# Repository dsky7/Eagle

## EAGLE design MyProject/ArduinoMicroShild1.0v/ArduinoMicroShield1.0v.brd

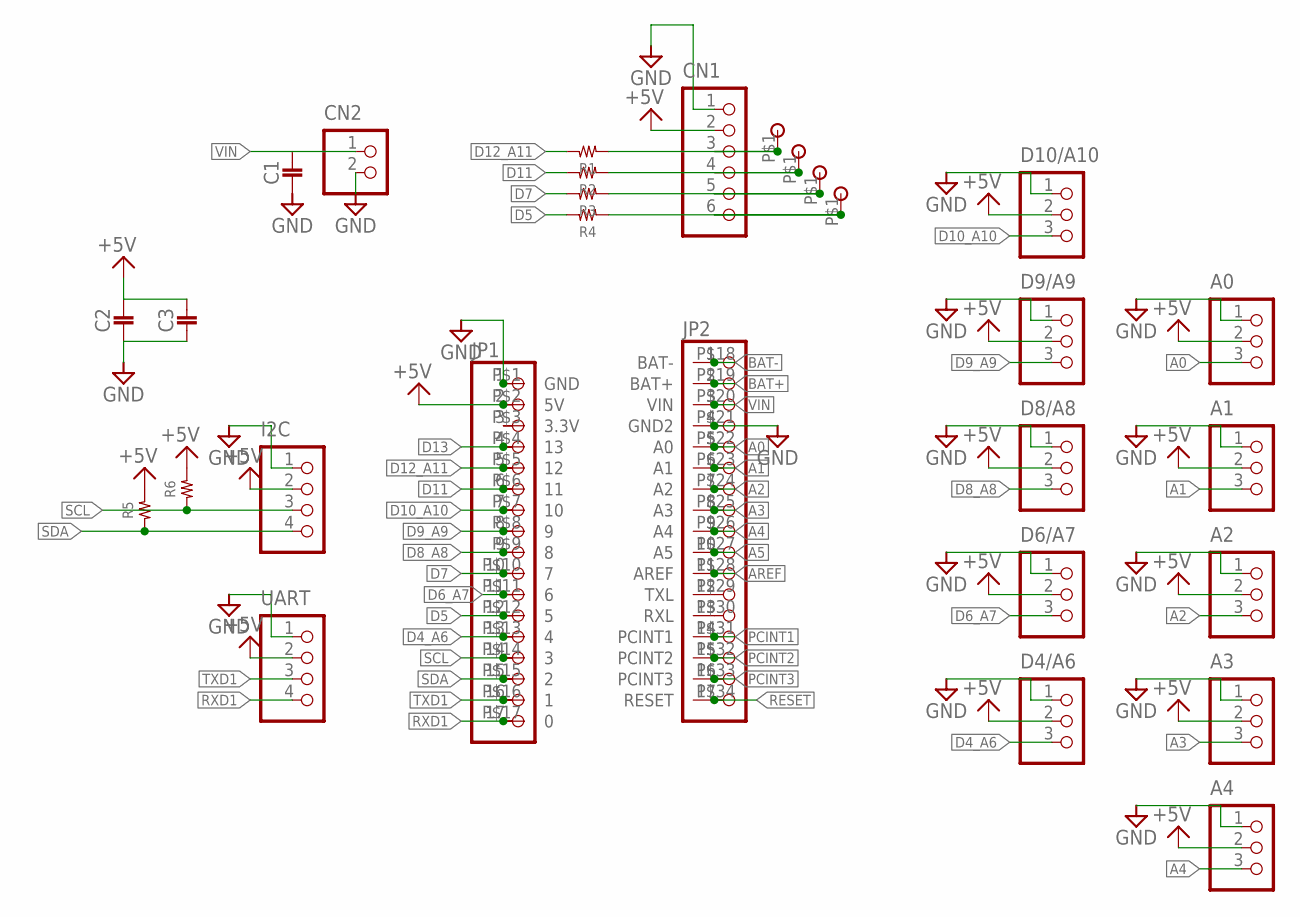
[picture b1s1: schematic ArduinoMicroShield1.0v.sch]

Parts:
A0, A1, A2, A3, A4: B3B-PH-K-S
C1, C2, C3: 1608
CN1: B6B-PH-K-S
CN2: S2B-PH-K-S
D4/A6, D6/A7, D8/A8, D9/A9, D10/A10: B3B-PH-K-S
I2C: B4B-PH-K-S
JP1, JP2: PINHD-1X17; 1X17
R1, R2, R3, R4, R5, R6: RESISTOR__SMD; 1608
U$1: ARDUINO_ASTAR_MICRO
U$31, U$32, U$36, U$37: CHECK_0.8MM
UART: B4B-PH-K-S

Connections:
+5V: A0.2, A1.2, A2.2, A3.2, A4.2, C2.P$1 (1), C3.P$1 (1), CN1.2, D4/A6.2, D6/A7.2, D8/A8.2, D9/A9.2, D10/A10.2, I2C.2, JP1.2, R5.2, R6.2, U$1.P$2 (5V), UART.2
A0: A0.3, JP2.5, U$1.P$22 (A0)
A1: A1.3, JP2.6, U$1.P$23 (A1)
A2: A2.3, JP2.7, U$1.P$24 (A2)
A3: A3.3, JP2.8, U$1.P$25 (A3)
A4: A4.3, JP2.9, U$1.P$26 (A4)
A5: JP2.10, U$1.P$27 (A5)
AREF: JP2.11, U$1.P$28 (AREF)
BAT+: JP2.2, U$1.P$19 (BAT+)
BAT-: JP2.1, U$1.P$18 (BAT-)
D4_A6: D4/A6.3, JP1.13, U$1.P$13 (4)
D5: JP1.12, R4.2, U$1.P$12 (5)
D6_A7: D6/A7.3, JP1.11, U$1.P$11 (6)
D7: JP1.10, R3.2, U$1.P$10 (7)
D8_A8: D8/A8.3, JP1.9, U$1.P$9 (8)
D9_A9: D9/A9.3, JP1.8, U$1.P$8 (9)
D10_A10: D10/A10.3, JP1.7, U$1.P$7 (10)
D11: JP1.6, R2.2, U$1.P$6 (11)
D12_A11: JP1.5, R1.2, U$1.P$5 (12)
D13: JP1.4, U$1.P$4 (13)
GND: A0.1, A1.1, A2.1, A3.1, A4.1, C1.P$2 (2), C2.P$2 (2), C3.P$2 (2), CN1.1, CN2.2, D4/A6.1, D6/A7.1, D8/A8.1, D9/A9.1, D10/A10.1, I2C.1, JP1.1, JP2.4, U$1.P$1 (GND), U$1.P$21 (GND2), UART.1
unnamed: CN1.6, R4.1, U$37.P$1
unnamed: CN1.5, R3.1, U$36.P$1
unnamed: CN1.4, R2.1, U$32.P$1
unnamed: CN1.3, R1.1, U$31.P$1
unnamed: JP1.3, U$1.P$3 (3.3V)
unnamed: JP2.12, U$1.P$29 (TXL)
unnamed: JP2.13, U$1.P$30 (RXL)
PCINT1: JP2.14, U$1.P$31 (PCINT1)
PCINT2: JP2.15, U$1.P$32 (PCINT2)
PCINT3: JP2.16, U$1.P$33 (PCINT3)
RESET: JP2.17, U$1.P$34 (RESET)
RXD1: JP1.17, U$1.P$17 (0), UART.4
SCL: I2C.3, JP1.14, R6.1, U$1.P$14 (3)
SDA: I2C.4, JP1.15, R5.1, U$1.P$15 (2)
TXD1: JP1.16, U$1.P$16 (1), UART.3
VIN: C1.P$1 (1), CN2.1, JP2.3, U$1.P$20 (VIN)

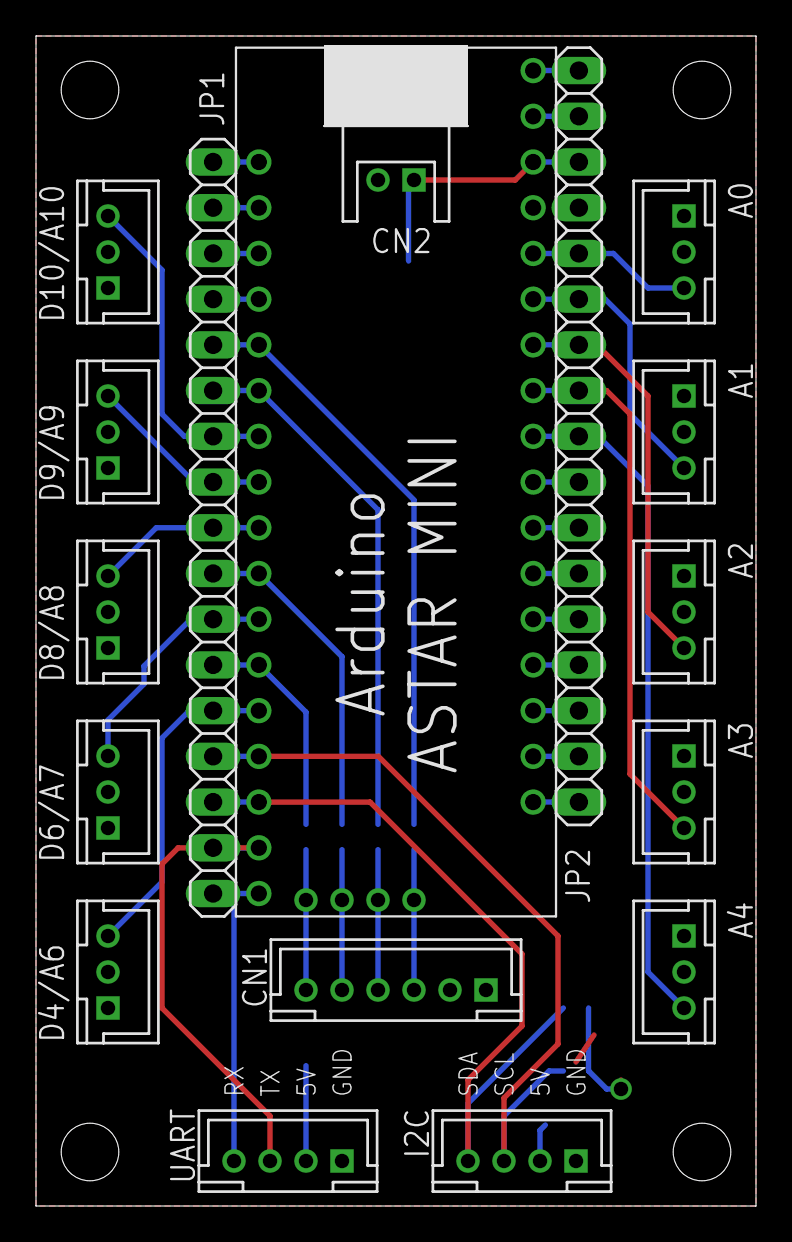
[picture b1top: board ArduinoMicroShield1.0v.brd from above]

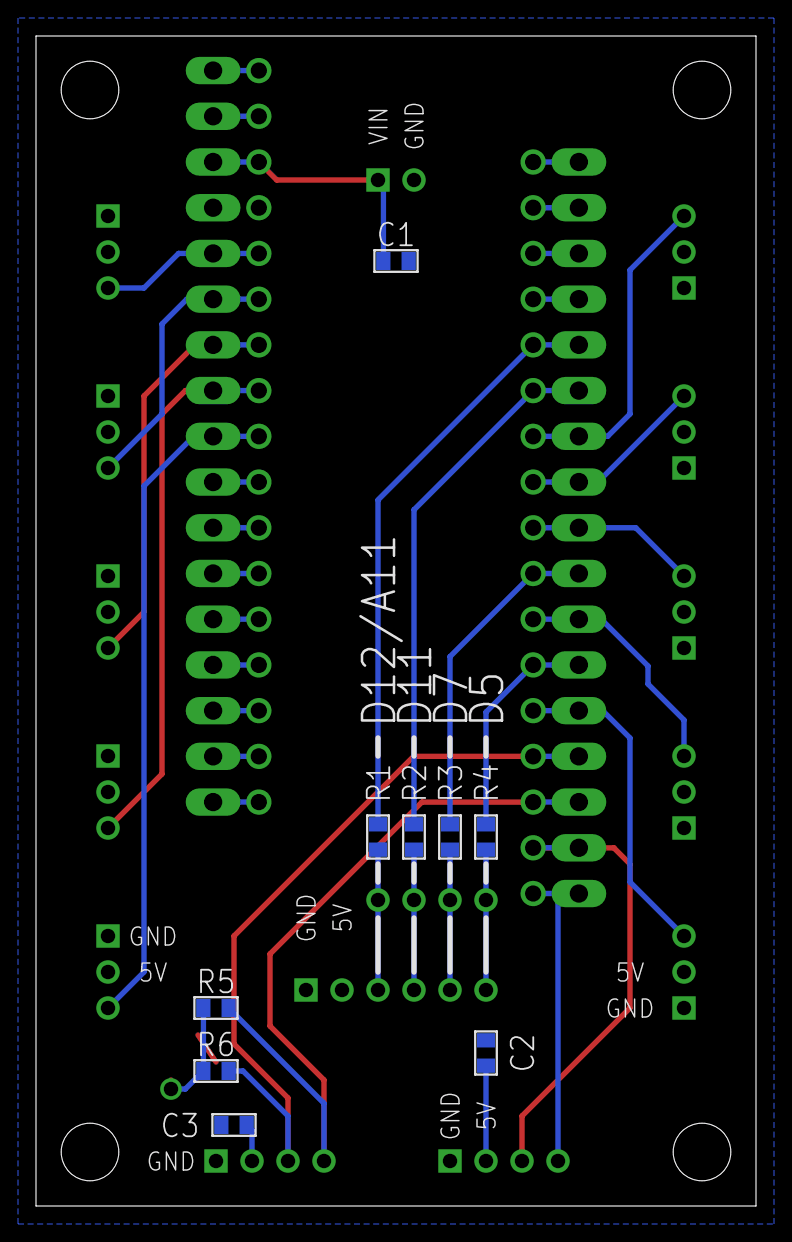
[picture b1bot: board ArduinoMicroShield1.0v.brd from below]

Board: 2 copper layers, 40.0 x 65.0 mm, 31 parts (9 on the bottom side), 37 nets.

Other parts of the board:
DRILEGEND: DRILEGEND

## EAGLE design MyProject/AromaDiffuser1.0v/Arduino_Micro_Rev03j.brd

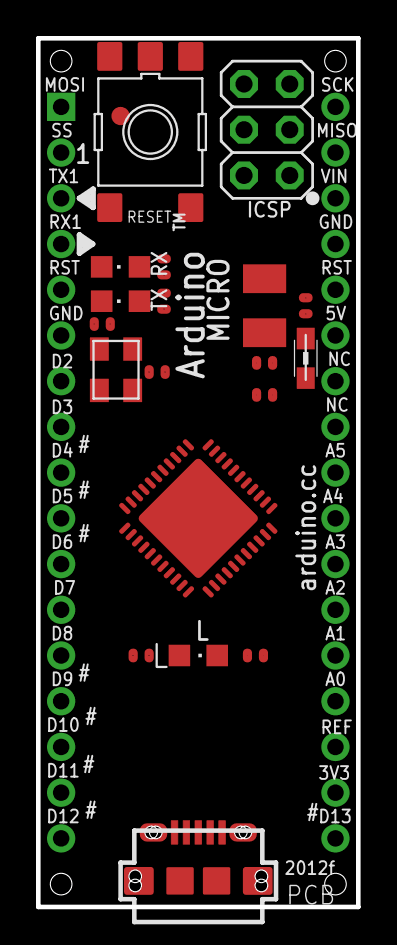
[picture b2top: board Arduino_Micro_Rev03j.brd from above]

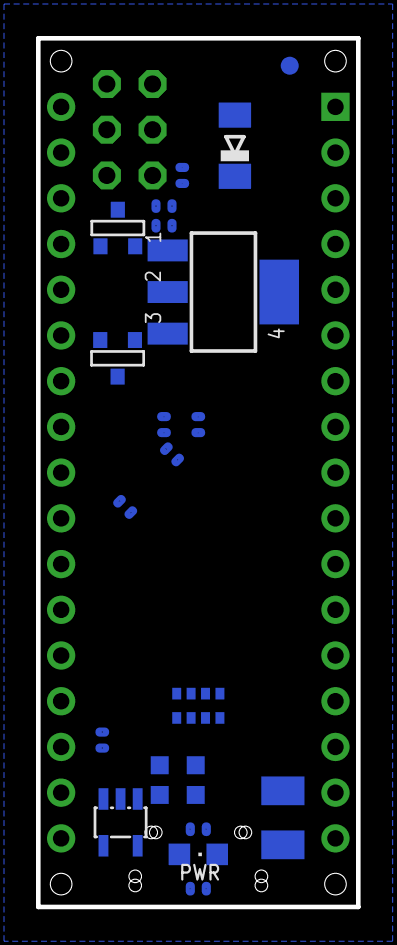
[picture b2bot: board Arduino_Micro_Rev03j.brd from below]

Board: 4 copper layers, 17.8 x 48.3 mm, 44 parts (21 on the bottom side), 47 nets, no tracks yet.

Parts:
C1, C2, C6, C9, C10, C11: 100n; C0402
C3, C14: 22u; SMC_B
C4, C5, C7: 1uF; C0402
C12, C13: 22pF; C0402
D2: CD1206-S01575; MINIMELF
J3: USB-MICRO!!!; CON2_USB_MICRO_B_AT
J4: 3x2M; 2X03
J5: HEAD17-NOSS
J6: HEAD17-NOSS-1
L: green; CHIPLED_0805
L2: MH2029-300Y; 0805
ON: blue; CHIPLED_0805
R1, R2, R4, R9: 10K; R0402
R5, R6, R7, R8: 1K; R0402
RESET: TS42
RP3: 22R; CAY16
RX: yellow; CHIPLED_0805
T1: FDN340P/PMV48XP; SOT-23
T2: PMV48XP; SOT-23
TX: yellow; CHIPLED_0805
U1: ATMEGA32U4-XUMU; QFN44ML7X7
U2: NCP1117-5; SOT223
U4: LP2985-33DBVR; SOT23-DBV
U$3: DISCLAIMER
U$37: FIDUCIALMOUNT; FIDUCIA-MOUNT
U$53: FIDUCIAL1X2; FIDUCIAL-1X2
Y3: 16MHz KX-7; CRYSTAL-3.2-2.5
Z1, Z2: CG0603MLC-05E; CT/CN0603

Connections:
3V3: C4.1, J6.16, U4.5
+5V: C2.1, C3.+, C10.1, C11.1, D2.C, J4.2, J6.6, L2.1, R1.1, R5.1, T1.2, T2.3, U1.2, U1.14, U1.24, U1.34, U2.2, U2.4, U4.1, U4.3
+VIN: C1.1, T2.2, U2.3
A0: J6.14, U1.36
A1: J6.13, U1.37
A2: J6.12, U1.38
A3: J6.11, U1.39
A4: J6.10, U1.40
A5: J6.9, U1.41
AREF: C6.1, J6.15, U1.42
AVCC: C7.1, L2.2, U1.44
D0/RX: J5.4, U1.20
D1/TX: J5.3, U1.21
D2/SDA: J5.7, U1.19
D3/SCL: J5.8, U1.18
D4*: J5.9, U1.25
D5*: J5.10, U1.31
D6*: J5.11, U1.27
D7: J5.12, U1.1
D+: J3.P3, RP3.8, Z1.1
D-: J3.P2, RP3.7, Z2.1
GND: C1.2, C2.2, C3.-, C4.2, C5.2, C6.2, C7.2, C9.2, C10.2, C11.2, C12.1, C13.1, C14.-, J3.P5, J3.S1, J3.S2, J3.S3, J3.S4, J3.S5, J3.S6, J4.6, J5.6, J6.4, L.C, ON.C, R2.1, R4.2, R9.1, RESET.3, RESET.4, RP3.3, RP3.4, RP3.5, RP3.6, RX.C, TX.C, U1.5, U1.15, U1.23, U1.35, U1.43, U1.EXP, U2.1, U4.2, Y3.2, Y3.4, Z1.2, Z2.2
HWB: R4.1, U1.33
IO8: J5.13, U1.28
IO9*: J5.14, U1.29
IO10*: J5.15, U1.30
IO11*: J5.16, U1.12
IO12*: J5.17, U1.26
IO13*: J6.17, R8.1, U1.32
MISO: J4.1, J6.2, U1.11
MOSI: J4.4, J5.1, U1.10
unnamed: R7.2, RX.A
unnamed: ON.A, R5.2
unnamed: R6.2, TX.A
unnamed: L.A, R8.2
RD+: RP3.1, U1.4
RD-: RP3.2, U1.3
RESET: D2.A, J4.5, J5.5, J6.5, R1.2, RESET.2, U1.13
RXLED/SS: J5.2, R7.1, U1.8
SCK: J4.3, J6.1, U1.9
TXLED: R6.1, U1.22
UCAP: C5.1, U1.6
VIN: J6.3, R9.2, T1.3, T2.1
VUSB: C9.1, R2.2, T1.1, U1.7
VUSBD: C14.+, J3.P1
XTAL1: C13.2, U1.17, Y3.3
XTAL2: C12.2, U1.16, Y3.1

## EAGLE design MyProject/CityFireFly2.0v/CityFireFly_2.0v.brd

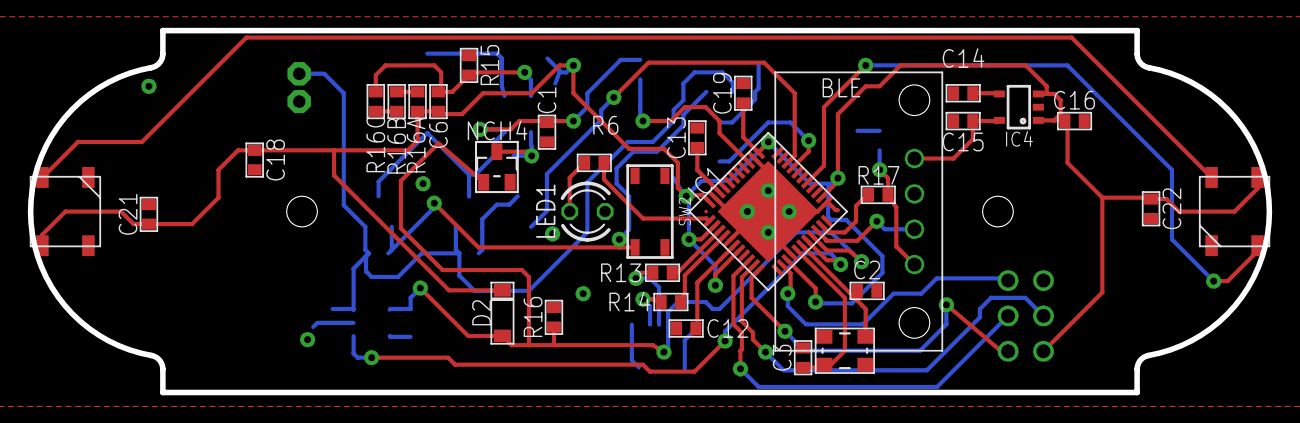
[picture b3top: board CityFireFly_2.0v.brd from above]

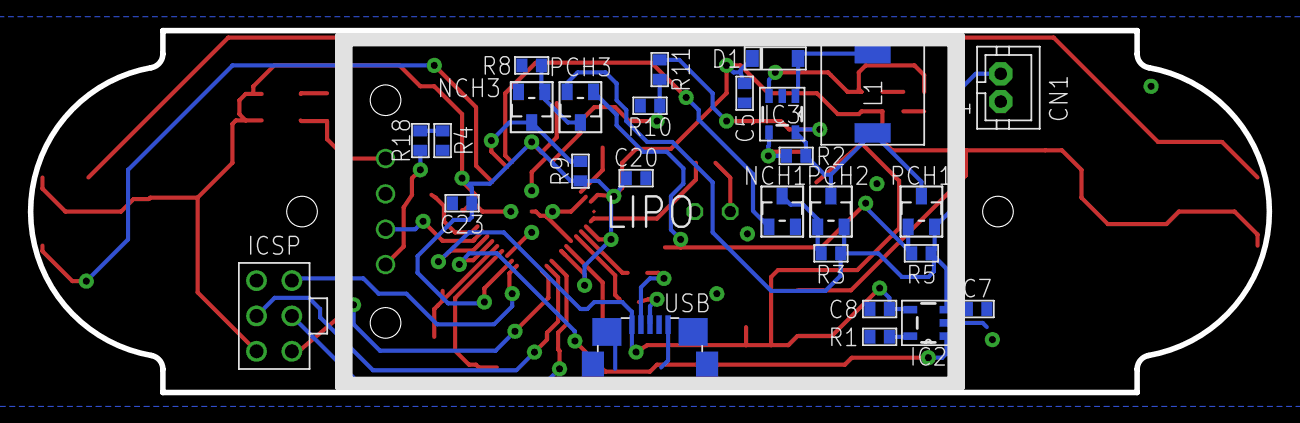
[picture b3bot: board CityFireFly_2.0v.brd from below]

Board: 2 copper layers, 89.0 x 26.0 mm, 60 parts (28 on the bottom side), 40 nets.

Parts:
BLE_SERIAL2: BLE_SERIAL2; BLESERIAL2
C1, C5: 22uF; 1608
C2, C3: 10pF; 1608
C6: 1nF; 1608
C7, C8: 4.7uF; 1608
C12, C16: 1uF; 1608
C13, C18, C19, C20: 0.1uF; 1608
C14: 0.01uF; 1608
C15, C23: 10uF; 1608
C21, C22: 47uF; 1608
CN1: JST-PH2
D1, D2: SOD-123; SOD_123
IC1: ATMEGA32U4; QFN-44-7X7
IC2: MCP73831; SOT23-5L
IC3: LM2735; SOT23-5L
IC4: TAR5SB; SSOP5-P-0.95
L1: D63; TOKO
LED1: 3MMLED; 3MM
LED2, LED3: NEO_FLAT
NCH1, NCH3, NCH4: CHIP_FET; SOT23
PCH1, PCH2, PCH3: CHIP_FET_P; SOT23
R1: 2K; 1608
R2: 100K; 1608
R3, R5, R8, R9, R10, R15, R16, R16A, R16B, R16C: 10K; 1608
R4: 470; 1608
R6: 330; 1608
R11, R17, R18: 1K; 1608
R13, R14: 22; 1608
SW2: SKRPACE010; SKRP
U$3: ICSP
U$73: LIPO750MAH
USB: MICRO-USB-KYORITU; ZX62R-B-5P
XTAL: FA-238

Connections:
+3.3V: BLE_SERIAL2.4, C15.P$1, IC4.5
+3.7V: C1.P$1, IC3.5, L1.1, PCH1.3, PCH2.3, R2.2, R11.2
+5V: C5.P$1, C6.P$1, C16.P$1, C18.P$1, C19.P$1, C20.P$1, C21.P$1, C22.P$1, C23.P$1, D1.C, D2.C, IC1.2, IC1.7, IC1.14, IC1.24, IC1.34, IC1.44, IC4.1, IC4.3, LED2.1, LED3.1, R9.2, R16A.2, U$3.2
+USB5V: C8.P$1, D2.A, IC1.19, IC2.4, NCH4.1, R16.2, USB.5
ADC0: IC1.36, R10.2, R11.1
ATOM: BLE_SERIAL2.1, R17.1, R18.2
D0: BLE_SERIAL2.2, IC1.20
D1: IC1.21, R17.2
D5: IC1.31, NCH1.1
D6: IC1.27, LED2.4
D7: IC1.1, R6.2
D10: IC1.30, NCH3.3, R9.1
D+: R14.2, USB.3
D-: R13.2, USB.4
DOUT: LED2.2, LED3.4
FB: C6.P$2, IC3.3, R15.2, R16C.1
GND: BLE_SERIAL2.3, C1.P$2, C2.P$2, C3.P$2, C5.P$2, C7.P$2, C8.P$2, C12.P$1, C13.P$2, C14.P$2, C15.P$2, C16.P$2, C18.P$2, C19.P$2, C20.P$2, C21.P$2, C22.P$2, C23.P$2, CN1.1, IC1.5, IC1.15, IC1.23, IC1.35, IC1.43, IC1.TH, IC2.2, IC3.2, IC4.2, LED1.K, LED2.3, LED3.3, NCH1.2, NCH3.2, NCH4.2, R1.1, R4.1, R8.1, R10.1, R15.1, R16.1, SW2.2, U$3.6, USB.1, USB.M1, USB.M2, USB.M3, USB.M4, XTAL.2, XTAL.4
MISO: IC1.11, U$3.1
MOSI: IC1.10, U$3.4
unnamed: LED1.A, R6.1
unnamed: IC2.5, R1.2
unnamed: IC3.4, NCH4.3, R2.1
unnamed: D1.A, IC3.1, L1.2
unnamed: R16A.1, R16B.2
unnamed: NCH1.3, PCH2.1, R3.1
unnamed: C3.P$1, IC1.16, XTAL.1
unnamed: IC1.3, R13.1
unnamed: C13.P$1, IC1.42
unnamed: C2.P$1, IC1.17, XTAL.3
unnamed: R16B.1, R16C.2
unnamed: R4.2, R18.1
unnamed: IC1.4, R14.1
unnamed: C14.P$1, IC4.4
unnamed: C12.P$2, IC1.6
RESET: IC1.13, U$3.5
SCLK: IC1.9, U$3.3
SIG: NCH3.1, PCH3.3, R8.2
STAT: IC1.18, IC2.1
SWSIG: PCH1.1, PCH3.1, R5.1, SW2.4
V2: C7.P$1, CN1.2, IC2.3, PCH1.2, PCH2.2, PCH3.2, R3.2, R5.2

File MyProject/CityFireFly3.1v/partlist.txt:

Partlist

Exported from CityFireFly_3.1v.brd at 2016/03/04 19:21

EAGLE Version 7.5.0 Copyright (c) 1988-2015 CadSoft

Assembly variant: 

Part     Value               Package            Library      Position (mm)         Orientation

BLE      BLE_SERIAL2_NO_HOLE BLESERIAL2_NO_HOLE 12_module    (30 5)                MR0
C1       22uF                1608               02_C         (25.5 13.1)           MR180
C2       10pF                1005               02_C         (43.7 3.9)            MR270
C3       10pF                1005               02_C         (49.5 3.9)            MR90
C5       22uF                1608               02_C         (27.2 18.5)           MR0
C6       1nF                 1005               02_C         (30 18.4)             MR0
C7       4.7uF               1005               02_C         (12.4 13.9)           R270
C8       4.7uF               1005               02_C         (15.2 14)             R180
C12      1uF                 1005               02_C         (43.45 18.85)         R0
C13      0.1uF               1005               02_C         (37 16.7)             MR45
C14      0.01uF              1608               02_C         (23.45 7.8)           R180
C15      10uF                1608               02_C         (23.4 5.9)            R180
C16      1uF                 1005               02_C         (29.1 7.3)            R270
C18      0.1uF               1005               02_C         (38.35 5.1)           MR225
C19      0.1uF               1005               02_C         (38.7 16.7)           MR315
C20      0.1uF               1005               02_C         (35 12.7)             MR135
C21      0.1uF               1005               02_C         (46.8 7.4)            MR270
C22      47uF                1608               02_C         (3.5 5.6)             MR0
C23      10uF                1608               02_C         (56.5 16)             MR180
CN1                          JST-PH2            jst-ph (1)   (9.4 16.1)            MR0
D1       SOD-123             SOD_123            15_DIODE     (26.2 20.4)           MR180
D2       SOD-123             SOD_123            15_DIODE     (12.3 6)              R180
FN1      CHIP_FET            SOT23              06_FET       (13.8 7.9)            MR0
FN4      CHIP_FET            SOT23              06_FET       (21.6 16.7)           R0
FNP1     SI1553CDL           SOT363             06_FET       (33.8 7)              R270
FPP      FDC6506P            SOT23-6            06_FET       (13.8 15.1)           MR90
IC1      ATMEGA32U4          QFN-44-7X7         04_IC        (40.5 11)             MR315
IC2      MCP73831            SOT23-5L           04_IC        (15.1 16.5)           R270
IC3      LM2735              SOT23-5L           04_IC        (26 15.8)             MR180
IC4      TAR5SB              SSOP5-P-0.95       04_IC        (26.7 6.9)            R90
L1       D63                 TOKO               03_L         (20.3 17)             MR90
LED1     3MMLED              3MM                10_LED       (27 11)               R90
LED2     NEO_FLAT            NEO_FLAT           10_LED       (56.5 11)             MR270
LED3     NEO_FLAT            NEO_FLAT           10_LED       (3.5 11)              MR90
R1       2K                  1005               01_R         (17.6 17)             R90
R2       100K                1005               01_R         (25.7 16.1)           R270
R3       10K                 1005               01_R         (11 13.9)             MR90
R4       1.5k                1005               01_R         (37.1 3.2)            MR180
R5       10K                 1005               01_R         (36.25 6.35)          R270
R6       330                 1005               01_R         (29.6 9.4)            MR180
R8       10K                 1005               01_R         (31.9 6.8)            R270
R9       10K                 1005               01_R         (34.8 5.8)            MR225
R11      1K                  1005               01_R         (34.8 14.7)           MR45
R13      22                  1005               01_R         (40.7 17.1)           R180
R14      22                  1005               01_R         (40.7 16.2)           R180
R15      10K                 1005               01_R         (30 16.8)             MR0
R16      10K                 1005               01_R         (20.5 3.4)            R270
R17      1K                  1005               01_R         (41 3.2)              R0
R18      30k                 1005               01_R         (30 17.6)             MR180
SW2      SKRPACE010          SKRP               09_1_switch  (41 11)               R270
U$3      ICSP                ICSP               08_CONECTOR  (49.3 16)             MR90
USB      USB_MICRO_VERTICAL  USB_MICRO_VERTICAL 08_CONECTOR  (19 11)               R0
XTAL     FA-238              FA-238             09_2_CRYSTAL (46.5 4.5)            MR0

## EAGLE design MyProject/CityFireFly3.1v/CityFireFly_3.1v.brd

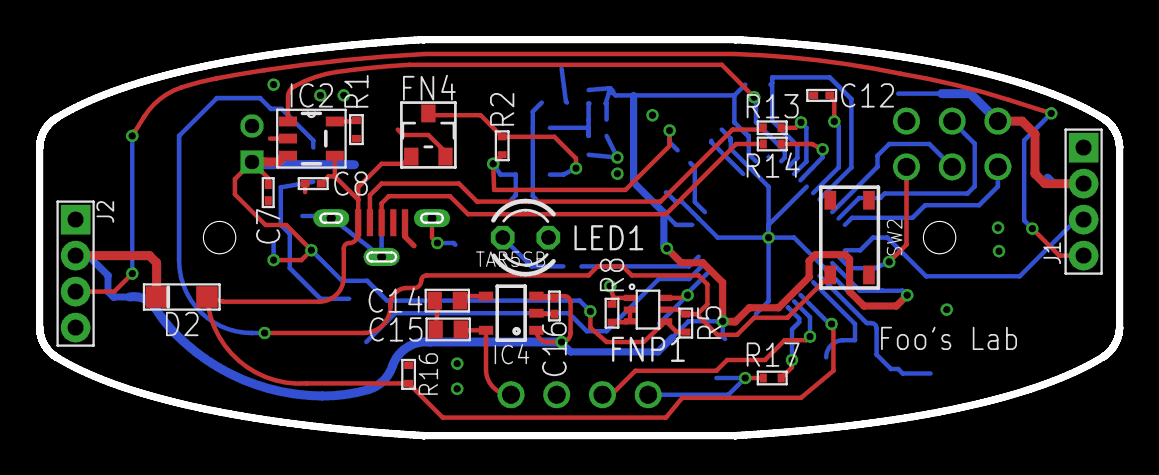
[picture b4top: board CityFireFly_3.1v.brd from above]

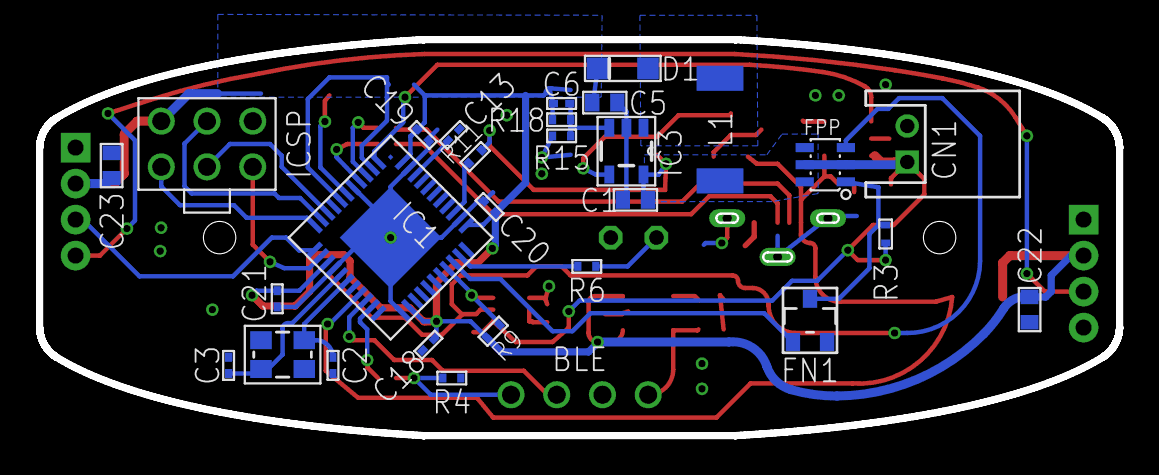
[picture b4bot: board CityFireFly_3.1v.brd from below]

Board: 2 copper layers, 60.0 x 22.0 mm, 54 parts (30 on the bottom side), 37 nets.

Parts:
BLE: BLE_SERIAL2_NO_HOLE; BLESERIAL2_NO_HOLE
C1, C5: 22uF; 1608
C2, C3: 10pF; 1005
C6: 1nF; 1005
C7, C8: 4.7uF; 1005
C12, C16: 1uF; 1005
C13, C18, C19, C20, C21: 0.1uF; 1005
C14: 0.01uF; 1608
C15, C23: 10uF; 1608
C22: 47uF; 1608
CN1: S2B-PH-K-S
D1, D2: SOD-123; SOD_123
FN1, FN4: CHIP_FET; SOT23
FNP1: SI1553CDL; SOT363
FPP: FDC6506P; SOT23-6
IC1: 32U4; QFN-44-7X7
IC2: MCP73831; SOT23-5L
IC3: LM2735; SOT23-5L
IC4: TAR5SB; SSOP5-P-0.95
J1, J2: 4P-2.0-65/35MIL-90D-FEMALE-LEFT
L1: D63; TOKO
LED1: 3MMLED; 3MM
R1: 2K; 1005
R2: 100K; 1005
R3, R5, R8, R9, R15, R16: 10K; 1005
R4: 1.5k; 1005
R6: 330; 1005
R11, R17: 1K; 1005
R13, R14: 22; 1005
R18: 30k; 1005
SW2: SKRPACE010; SKRP
U$3: ICSP
U$68: LIPO500MAH
USB: USB_MICRO_VERTICAL_D
XTAL: FA-238

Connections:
+3.3V: BLE.4, C15.P$1, IC4.5
+3.7V: C1.P$1, FPP.4, FPP.6, IC3.5, L1.1, R2.2, R11.2
+5V: C5.P$1, C6.1, C16.1, C18.1, C19.1, C20.1, C21.1, C22.P$1, C23.P$1, D1.C, D2.C, IC1.2, IC1.7, IC1.14, IC1.24, IC1.34, IC1.44, IC4.1, IC4.3, J1.2, J2.2, R9.2, R18.2, U$3.2
+USB5V: C8.1, D2.A, FN4.1, IC1.19, IC2.4, R16.2, USB.1
ADC0: IC1.36, R11.1
ATOM: BLE.1, R4.2, R17.1
D0: BLE.2, IC1.20
D1: IC1.21, R17.2
D5: FN1.1, IC1.31
D7: IC1.1, IC2.1
D10: FNP1.6, IC1.30, R9.1
D11: IC1.12, J1.3
D13: IC1.32, R6.2
D+: R14.2, USB.3
D-: R13.2, USB.2
DL: D1.A, IC3.1, L1.2
DOUT: J1.4, J2.3
FB: C6.2, IC3.3, R15.2, R18.1
GND: BLE.3, C1.P$2, C2.2, C3.2, C5.P$2, C7.2, C8.2, C12.1, C13.2, C14.P$2, C15.P$2, C16.2, C18.2, C19.2, C20.2, C21.2, C22.P$2, C23.P$2, CN1.2, FN1.2, FN4.2, FNP1.1, IC1.5, IC1.15, IC1.23, IC1.35, IC1.43, IC1.TH, IC2.2, IC3.2, IC4.2, J1.1, J2.1, LED1.K, R1.1, R4.1, R8.1, R15.1, R16.1, SW2.2, U$3.6, USB.5, USB.S6, USB.S7, USB.S8, XTAL.2, XTAL.4
MISO: IC1.11, U$3.1
MOSI: IC1.10, U$3.4
unnamed: LED1.A, R6.1
unnamed: IC2.5, R1.2
unnamed: FN4.3, IC3.4, R2.1
unnamed: FN1.3, FPP.1, R3.1
unnamed: C3.1, IC1.16, XTAL.1
unnamed: IC1.3, R13.1
unnamed: C13.1, IC1.42
unnamed: C2.1, IC1.17, XTAL.3
unnamed: IC1.4, R14.1
unnamed: C14.P$1, IC4.4
unnamed: C12.2, IC1.6
RESET: IC1.13, U$3.5
SCLK: IC1.9, U$3.3
SIG: FNP1.2, FNP1.3, R8.2
SWSIG: FNP1.5, FPP.3, R5.1, SW2.4
V2: C7.1, CN1.1, FNP1.4, FPP.2, FPP.5, IC2.3, R3.2, R5.2

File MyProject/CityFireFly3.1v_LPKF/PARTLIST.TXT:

Partlist

Exported from CityFireFly_3.1v_LPKF.sch at 2016/03/11 16:50

EAGLE Version 7.5.0 Copyright (c) 1988-2015 CadSoft

Assembly variant: 

Part     Value                   Device                  Package                         Library      Sheet

BLE      BLE_SERIAL2_NO_HOLE     BLE_SERIAL2_NO_HOLE     BLESERIAL2_NO_HOLE              12_module    1
C1       22uF                    1608                    1608                            02_C         1
C2       10pF                    1005                    1005                            02_C         1
C3       10pF                    1005                    1005                            02_C         1
C5       22uF                    1608                    1608                            02_C         1
C6       1nF                     1005                    1005                            02_C         1
C7       4.7uF                   1005                    1005                            02_C         1
C8       4.7uF                   1005                    1005                            02_C         1
C12      1uF                     1005                    1005                            02_C         1
C13      0.1uF                   1005                    1005                            02_C         1
C14      0.01uF                  1608                    1608                            02_C         1
C15      10uF                    1608                    1608                            02_C         1
C16      1uF                     1005                    1005                            02_C         1
C18      0.1uF                   1005                    1005                            02_C         1
C19      0.1uF                   1005                    1005                            02_C         1
C20      0.1uF                   1005                    1005                            02_C         1
C21      0.1uF                   1005                    1005                            02_C         1
C22      47uF                    1608                    1608                            02_C         1
C23      10uF                    1608                    1608                            02_C         1
CN1                              S2B-PH-K-S              S2B-PH-K-S                      jst-ph1      1
D1       SOD-123                 SOD-123                 SOD_123                         15_DIODE     1
D2       SOD-123                 SOD-123                 SOD_123                         15_DIODE     1
FN1      CHIP_FET                CHIP_FET                SOT23                           06_FET       1
FN4      CHIP_FET                CHIP_FET                SOT23                           06_FET       1
FNP1     SI1553CDL               SI1553CDL               SOT363                          06_FET       1
FPP      FDC6506P                FDC6506P                SOT23-6                         06_FET       1
IC1      ATMEGA32U4              ATMEGA32U4              QFN-44-7X7                      04_IC        1
IC2      MCP73831                MCP73831                SOT23-5L                        04_IC        1
IC3      LM2735                  LM2735                  SOT23-5L                        04_IC        1
IC4      TAR5SB                  TAR5SB                  SSOP5-P-0.95                    04_IC        1
J1                               HEADER-4PFEMALE-LEFT    4P-2.0-65/35MIL-90D-FEMALE-LEFT Connector    1
J2                               HEADER-4PFEMALE-LEFT    4P-2.0-65/35MIL-90D-FEMALE-LEFT Connector    1
L1       D63                     D63                     TOKO                            03_L         1
LED1     3MMLED                  3MMLED                  3MM                             10_LED       1
R1       2K                      RESISTOR_1005           1005                            01_R         1
R2       100K                    RESISTOR_1005           1005                            01_R         1
R3       10K                     RESISTOR_1005           1005                            01_R         1
R4       1.5k                    RESISTOR_1005           1005                            01_R         1
R5       10K                     RESISTOR_1005           1005                            01_R         1
R6       330                     RESISTOR_1005           1005                            01_R         1
R8       10K                     RESISTOR_1005           1005                            01_R         1
R9       10K                     RESISTOR_1005           1005                            01_R         1
R11      1K                      RESISTOR_1005           1005                            01_R         1
R13      22                      RESISTOR_1005           1005                            01_R         1
R14      22                      RESISTOR_1005           1005                            01_R         1
R15      10K                     RESISTOR_1005           1005                            01_R         1
R16      10K                     RESISTOR_1005           1005                            01_R         1
R17      1K                      RESISTOR_1005           1005                            01_R         1
R18      30k                     RESISTOR_1005           1005                            01_R         1
SW2      SKRPACE010              SKRPACE010              SKRP                            09_1_switch  1
U$3      ICSP                    ICSP                    ICSP                            08_CONECTOR  1
U$8      USB_MICRO_VERTICAL_LPKF USB_MICRO_VERTICAL_LPKF USB_MICRO_VERTICAL_LPKF         08_CONECTOR  1
U$32     USB_MICRO_VERTICAL      USB_MICRO_VERTICAL      USB_MICRO_VERTICAL              08_CONECTOR  1
USB      USB_MICRO_VERTICAL_D    USB_MICRO_VERTICAL_D    USB_MICRO_VERTICAL_D            08_CONECTOR  1
XTAL     FA-238                  FA-238                  FA-238                          09_2_CRYSTAL 1
